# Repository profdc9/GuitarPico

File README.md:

# Guitar Pico

This is a guitar effects processor based on the Raspberry Pi Pico.  A video of some of the effects is at

https://www.youtube.com/watch?v=15d9mEu2koQ

It includes the following effects:

1.  Noise Gate
2.  Delay 
3.  Room (set up specific echoes at particular delays)
4.  Combine (mix together the signals from several effects)
5.  2nd order Bandpass filter
6.  2nd order Lowpass filter
7.  2nd order Highpass filter
8.  2nd order Allpass filter
9.  Tremolo (amplitude modulated by a low frequency oscillator)
10.  Vibrato (pitch modulated by a low frequency oscillator)
11.  Wah (bandpass filter with center frequency controlled by an external control like a pedal)
12.  AutoWah (bandpass filter with center frequency modulated by a low frequency oscillator)
13.  Envelope (bandpass filter with center frequency modulated by signal amplitude)
14.  Distortion (amplification resulting in saturation of the signal)
15.  Overdrive (selectable threshold for low signal / high signal amplitude gain)
16.  Compressor (amplifies weak signals to equal out overall amplitude of signal)
17.  Ring (ring modulator using low frequency oscillator)
18.  Flanger (pitch modulated by a low frequency oscillator, with feedback and combined with unmodulated signal)
19.  Chorus (pitch modulated by a low frequency oscillator, no feedback and combined with unmodulated signal)
20.  Phaser (signal run through multiple stages of all pass filters, combined with unmodulated signal)
21.  Backwards (plays the last samples backwards for weird swooping effect)
22.  PitchShift (allows shifting the pitch by variable amounts, useful for harmony-like effect)
23.  Whammy (pitch shift based on external control like a pedal)
24.  Octave (rectification and amplification of the signal with extreme distortion)
25.  Sinusoidal Oscillator (built in test signal source)

The effects may be cascaded, to up to 16 in a sequence.  The settings of a particular sequence of effects may be saved in flash memory.  Because the effects are processed one sample at a time in real-time, the lag due to the processing is only 50 microseconds.

There is a stomp pedal which may be used to one of four saved settings, based on which of the four buttons is stomped on.  It does not require power to operate.

The pedal has four potentiometers that may be assigned to control various aspects of effects operation.  There are also two external inputs.  These can be used with the stomp pedal, or with an expression pedal to control aspects of the effects.

There is also a feature to determine the frequency and note being played, to help with tuning a guitar.  Also, if plugged into USB, notes played on the guitar are sent as MIDI events to the PC to turn the guitar into a MIDI instruments.  However, this feature is imperfect (but this useful for tuning).

As well as a MIDI device, the guitar pedal appears as a COM port.  The effect settings may be retrieved from the pedal or programmed into the pedal through this interface using text commands at a prompt.  Type "HELP" for a list of the commands.  For example, typing "CONF 0 0" lists all of the current effects configuration data.  The data is output in the form of the commands used to reprogram the same state back into the device, so these may be directly copied into a text file and pasted back into a terminal to recreate the configuration.

There is also a VGA port that will be used to implement video effects.

The hardware is licensed under CC-BY-SA 4.0 and software under the zlib license (no warranty, yes commercial and noncommercial use), both open source licenses.

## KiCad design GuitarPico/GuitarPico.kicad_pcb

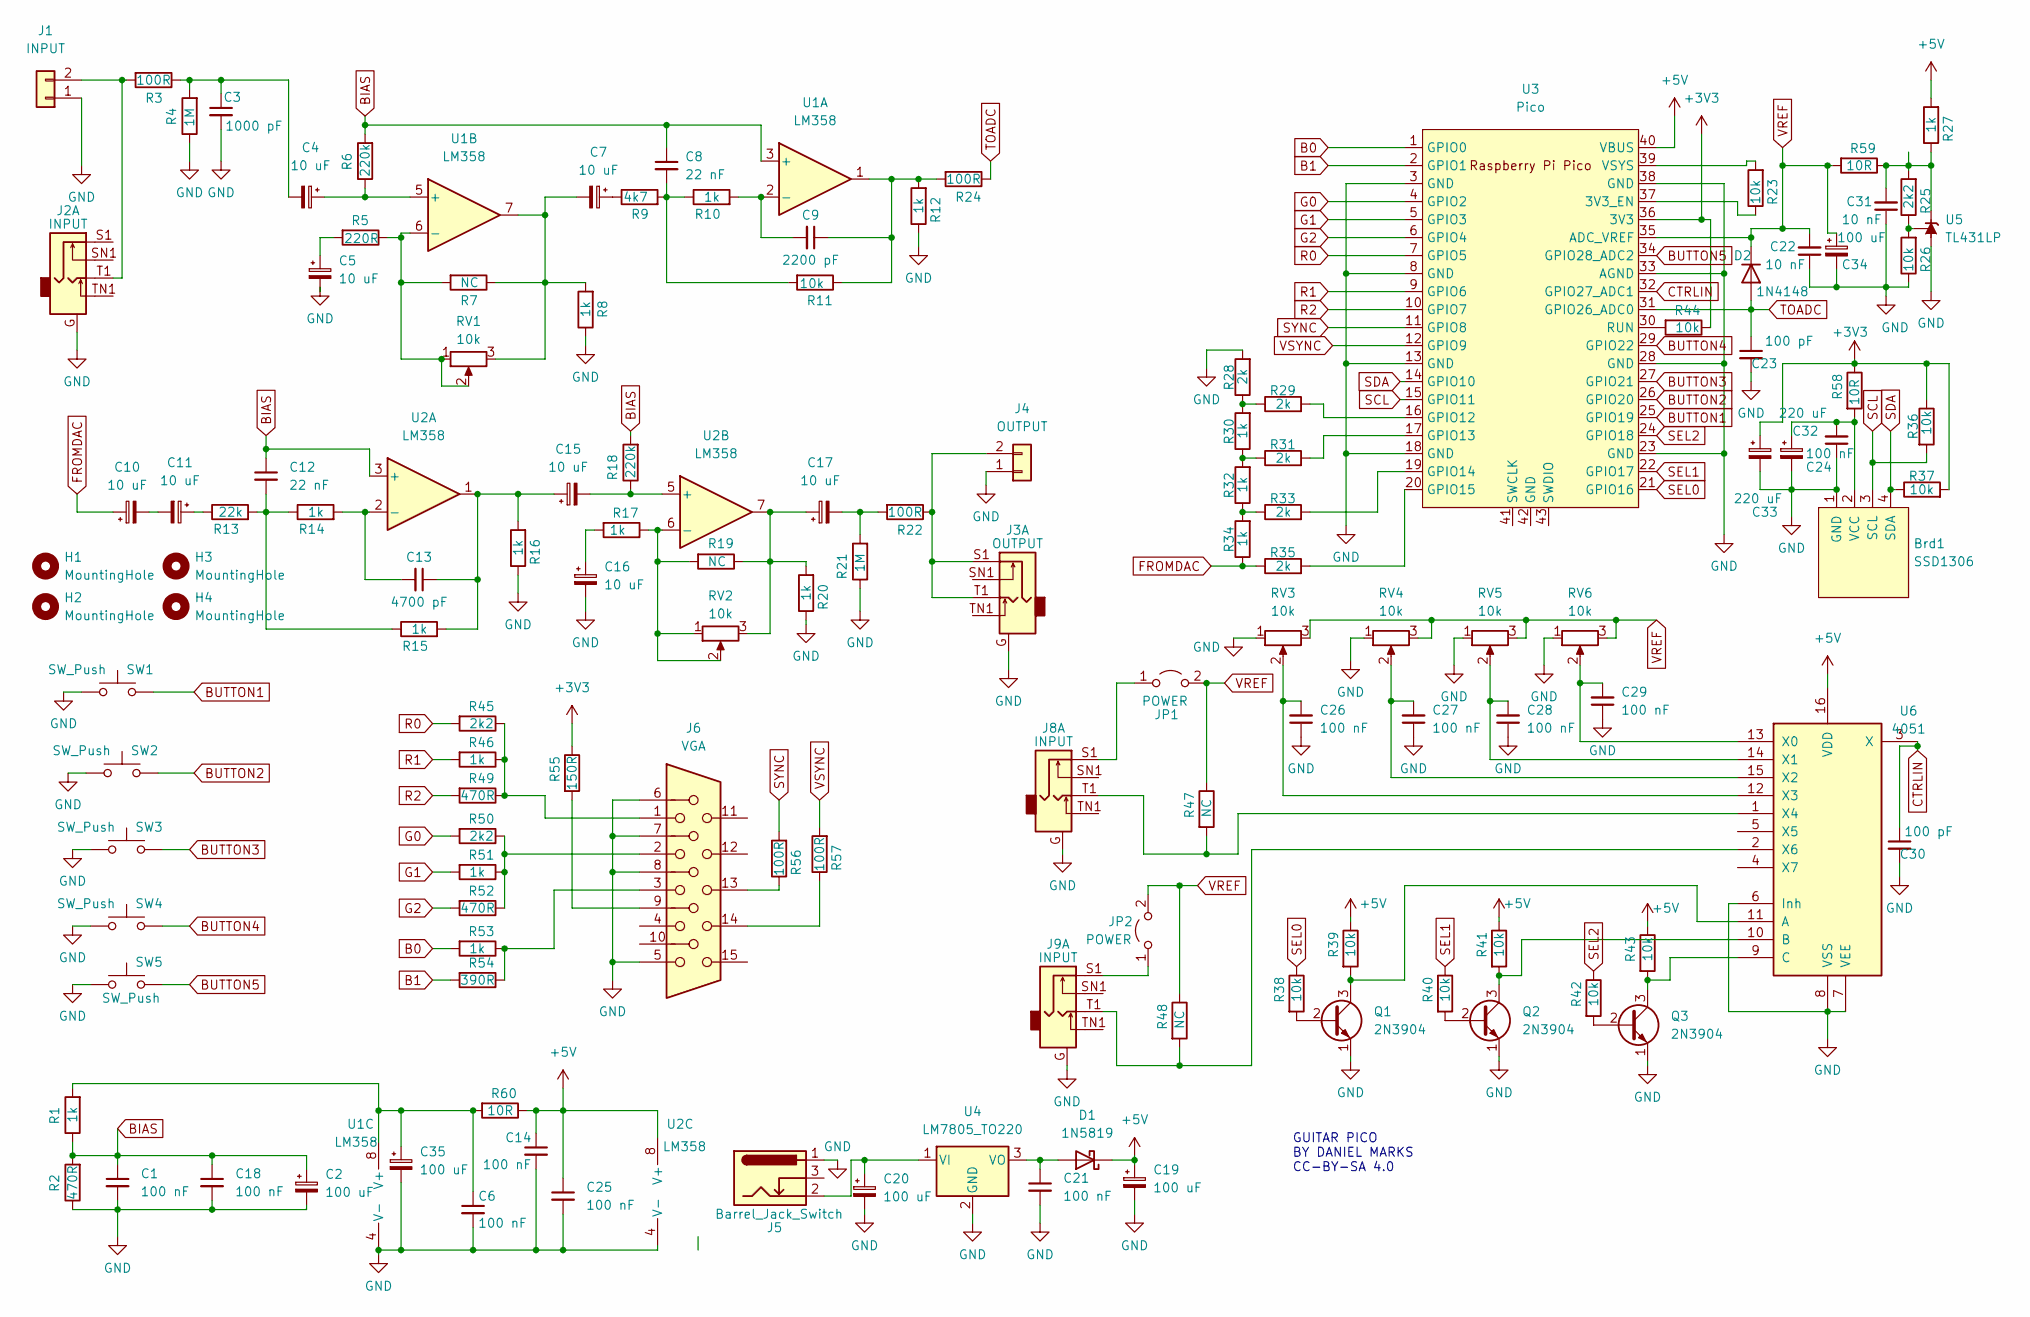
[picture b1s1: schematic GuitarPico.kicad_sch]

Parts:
Brd1: SSD1306; 128x64OLED
C1, C6, C14, C18, C21, C24, C25, C26, C27, C28, C29: 100 nF; C_Disc_D5.0mm_W2.5mm_P5.00mm
C2, C19, C20, C34, C35: 100 uF; CP_Radial_D5.0mm_P2.50mm
C3: 1000 pF; C_Disc_D5.0mm_W2.5mm_P5.00mm
C4, C5, C7, C10, C11, C15, C16, C17: 10 uF; CP_Radial_D5.0mm_P2.50mm
C8, C12: 22 nF; C_Disc_D5.0mm_W2.5mm_P5.00mm
C9: 2200 pF; C_Disc_D5.0mm_W2.5mm_P5.00mm
C13: 4700 pF; C_Disc_D5.0mm_W2.5mm_P5.00mm
C22, C31: 10 nF; C_Disc_D5.0mm_W2.5mm_P5.00mm
C23, C30: 100 pF; C_Disc_D5.0mm_W2.5mm_P5.00mm
C32, C33: 220 uF; CP_Radial_D5.0mm_P2.50mm
D1: 1N5819; D_DO-41_SOD81_P7.62mm_Horizontal
D2: 1N4148; D_DO-35_SOD27_P7.62mm_Horizontal
H1, H2, H3, H4: MountingHole; MountingHole_3.2mm_M3
J1: INPUT; TerminalBlock_bornier-2_P5.08mm
J2, J8, J9: INPUT; PJ-3240-35mm-stereo
J3: OUTPUT; PJ-3240-35mm-stereo
J4: OUTPUT; TerminalBlock_bornier-2_P5.08mm
J5: Barrel_Jack_Switch; BarrelJack_Horizontal
J6: VGA; DSUB-15-HD_Female_Horizontal_P2.29x1.98mm_EdgePinOffset3.03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
JP1, JP2: POWER; PinHeader_1x02_P2.54mm_Vertical
Q1, Q2, Q3: 2N3904; TO-92_Inline_Wide
R1, R8, R10, R12, R14, R15, R16, R17, R20, R27, R30, R32, R34, R46, R51, R53: 1k; R_Axial_DIN0207_L6.3mm_D2.5mm_P7.62mm_Horizontal
R2, R49, R52: 470R; R_Axial_DIN0207_L6.3mm_D2.5mm_P7.62mm_Horizontal
R3, R22, R24, R56, R57: 100R; R_Axial_DIN0207_L6.3mm_D2.5mm_P7.62mm_Horizontal
R4, R21: 1M; R_Axial_DIN0207_L6.3mm_D2.5mm_P7.62mm_Horizontal
R5: 220R; R_Axial_DIN0207_L6.3mm_D2.5mm_P7.62mm_Horizontal
R6, R18: 220k; R_Axial_DIN0207_L6.3mm_D2.5mm_P7.62mm_Horizontal
R7, R19, R47, R48: NC; R_Axial_DIN0207_L6.3mm_D2.5mm_P7.62mm_Horizontal
R9: 4k7; R_Axial_DIN0207_L6.3mm_D2.5mm_P7.62mm_Horizontal
R11, R23, R26, R36, R37, R38, R39, R40, R41, R42, R43, R44: 10k; R_Axial_DIN0207_L6.3mm_D2.5mm_P7.62mm_Horizontal
R13: 22k; R_Axial_DIN0207_L6.3mm_D2.5mm_P7.62mm_Horizontal
R25, R45, R50: 2k2; R_Axial_DIN0207_L6.3mm_D2.5mm_P7.62mm_Horizontal
R28, R29, R31, R33, R35: 2k; R_Axial_DIN0207_L6.3mm_D2.5mm_P7.62mm_Horizontal
R54: 390R; R_Axial_DIN0207_L6.3mm_D2.5mm_P7.62mm_Horizontal
R55: 150R; R_Axial_DIN0207_L6.3mm_D2.5mm_P7.62mm_Horizontal
R58, R59, R60: 10R; R_Axial_DIN0207_L6.3mm_D2.5mm_P7.62mm_Horizontal
RV1, RV2: 10k; Potentiometer_Big_Small_Combined
RV3, RV4, RV5, RV6: 10k; Potentiometer_Alps_RK09K_Single_Vertical
SW1, SW2, SW3, SW4, SW5: SW_Push; SW_PUSH_6mm
U1, U2: LM358; DIP-8_W7.62mm_Socket
U3: Pico; RPi_Pico_SMD_TH
U4: LM7805_TO220; TO-220-3_Vertical
U5: TL431LP; TO-92_Inline_Wide
U6: 4051; DIP-16_W7.62mm_Socket

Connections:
+3V3: C33.1, R36.1, R37.2, R44.1, R55.1, R58.1, U3.36 (3V3)
+5V: C14.1, C19.1, C25.1, D1.1 (K), R27.2, R39.1, R41.1, R43.1, R60.1, U2.8 (V+), U3.40 (VBUS), U6.16 (VDD)
B0: R53.2, U3.1 (GPIO0)
B1: R54.2, U3.2 (GPIO1)
BIAS: C1.1, C2.1, C8.1, C12.1, C18.1, R1.1, R2.2, R6.2, R18.2, U1.3 (+), U2.3 (+)
BUTTON1: SW1.2, U3.25 (GPIO19)
BUTTON2: SW2.2, U3.26 (GPIO20)
BUTTON3: SW3.2, U3.27 (GPIO21)
BUTTON4: SW4.2, U3.29 (GPIO22)
BUTTON5: SW5.2, U3.34 (GPIO28_ADC2)
CTRLIN: C30.1, U3.32 (GPIO27_ADC1), U6.3 (X)
FROMDAC: C10.1, R34.1, R35.1
G0: R50.2, U3.4 (GPIO2)
G1: R51.2, U3.5 (GPIO3)
G2: R52.2, U3.6 (GPIO4)
GND: Brd1.1 (GND), C1.2, C2.2, C3.2, C5.2, C6.2, C14.2, C16.2, C18.2, C19.2, C20.2, C21.2, C22.1, C23.2, C24.1, C25.2, C26.1, C27.1, C28.1, C29.1, C30.2, C31.1, C32.2, C33.2, C34.2, C35.2, J1.1, J2.G, J3.G, J4.1, J5.1, J6.5, J6.6, J6.7, J6.8, J8.G, J9.G, Q1.1 (E), Q2.1 (E), Q3.1 (E), R2.1, R4.1, R8.1, R12.1, R16.1, R20.1, R21.1, R26.1, R28.2, RV3.1, RV4.1, RV5.1, RV6.1, SW1.1, SW2.1, SW3.1, SW4.1, SW5.1, U1.4 (V-), U2.4 (V-), U3.3 (GND), U3.8 (GND), U3.13 (GND), U3.18 (GND), U3.23 (GND), U3.28 (GND), U3.33 (AGND), U3.38 (GND), U4.2 (GND), U5.2 (A), U6.6 (Inh), U6.7 (VEE), U6.8 (VSS)
unnamed: Brd1.2 (VCC), C24.2, C32.1, R58.2
unnamed: C3.1, C4.2, R3.1, R4.2
unnamed: C5.1, R5.2
unnamed: C7.1, R9.1
unnamed: C7.2, R7.1, R8.2, RV1.3, U1.7
unnamed: C8.2, R9.2, R10.1, R11.2
unnamed: C9.1, R11.1, R12.2, R24.2, U1.1
unnamed: C10.2, C11.2
unnamed: C11.1, R13.1
unnamed: C12.2, R13.2, R14.1, R15.1
unnamed: C13.1, C15.1, R15.2, R16.2, U2.1
unnamed: C16.1, R17.2
unnamed: C17.1, R19.1, R20.2, RV2.3, U2.7
unnamed: C17.2, R21.2, R22.2
unnamed: C21.1, D1.2 (A), U4.3 (VO)
unnamed: J1.2, J2.T1, R3.2
unnamed: J3.S1, J3.T1, J4.2, R22.1
unnamed: J6.1, R45.1, R46.1, R49.1
unnamed: J6.2, R50.1, R51.1, R52.1
unnamed: J6.3, R53.1, R54.1
unnamed: J6.9, R55.2
unnamed: J6.13, R56.1
unnamed: J6.14, R57.1
unnamed: J8.S1, JP1.1 (A)
unnamed: J9.S1, JP2.1 (A)
unnamed: Q1.2 (B), R38.2
unnamed: Q1.3 (C), R39.2, U6.11 (A)
unnamed: Q2.2 (B), R40.2
unnamed: Q2.3 (C), R41.2, U6.10 (B)
unnamed: Q3.2 (B), R42.2
unnamed: Q3.3 (C), R43.2, U6.9 (C)
unnamed: R28.1, R29.1, R30.2
unnamed: R30.1, R31.1, R32.2
unnamed: R32.1, R33.1, R34.2
unnamed: C9.2, R10.2, U1.2 (-)
unnamed: C4.1, R6.1, U1.5 (+)
unnamed: R5.1, R7.2, RV1.1, RV1.2, U1.6 (-)
unnamed: C6.1, C35.1, R1.2, R60.2, U1.8 (V+)
unnamed: C13.2, R14.2, U2.2 (-)
unnamed: C15.2, R18.1, U2.5 (+)
unnamed: R17.1, R19.2, RV2.1, RV2.2, U2.6 (-)
unnamed: R23.1, U3.37 (3V3_EN)
unnamed: R29.2, U3.16 (GPIO12)
unnamed: R31.2, U3.17 (GPIO13)
unnamed: R33.2, U3.19 (GPIO14)
unnamed: R35.2, U3.20 (GPIO15)
unnamed: R44.2, U3.30 (RUN)
unnamed: R23.2, U3.39 (VSYS)
unnamed: C20.1, J5.2, U4.1 (VI)
unnamed: C31.2, R25.2, R27.1, R59.1, U5.3 (K)
unnamed: R25.1, R26.2, U5.1 (REF)
unnamed: C29.2, RV6.2, U6.13 (X0)
unnamed: C28.2, RV5.2, U6.14 (X1)
unnamed: C27.2, RV4.2, U6.15 (X2)
unnamed: C26.2, RV3.2, U6.12 (X3)
unnamed: J8.T1, R47.2, U6.1 (X4)
unnamed: J9.T1, R48.2, U6.2 (X6)
R0: R45.2, U3.7 (GPIO5)
R1: R46.2, U3.9 (GPIO6)
R2: R49.2, U3.10 (GPIO7)
SCL: Brd1.3 (SCL), R36.2, U3.15 (GPIO11)
SDA: Brd1.4 (SDA), R37.1, U3.14 (GPIO10)
SEL0: R38.1, U3.21 (GPIO16)
SEL1: R40.1, U3.22 (GPIO17)
SEL2: R42.1, U3.24 (GPIO18)
SYNC: R56.2, U3.11 (GPIO8)
TOADC: C23.1, D2.2 (A), R24.1, U3.31 (GPIO26_ADC0)
VREF: C22.2, C34.1, D2.1 (K), JP1.2 (B), JP2.2 (B), R47.1, R48.1, R59.2, RV3.3, RV4.3, RV5.3, RV6.3, U3.35 (ADC_VREF)
VSYNC: R57.2, U3.12 (GPIO9)

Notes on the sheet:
GUITAR PICO BY DANIEL MARKS CC-BY-SA 4.0

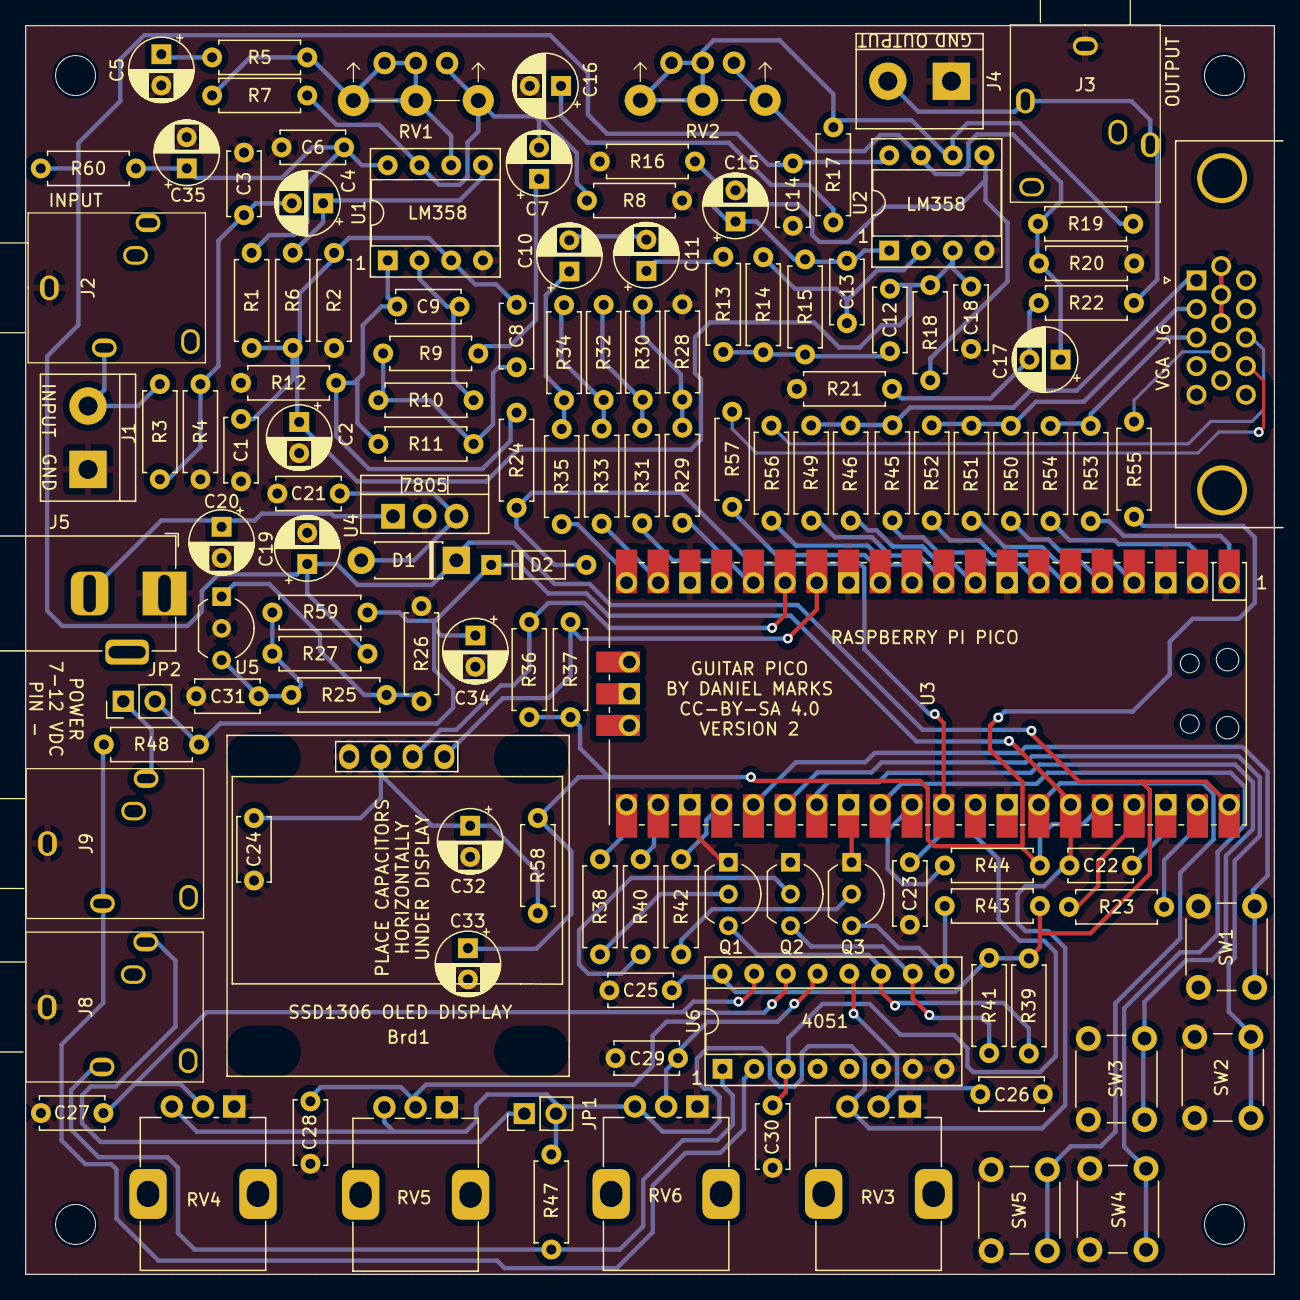
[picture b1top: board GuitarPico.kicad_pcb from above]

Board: 2 copper layers, 100.0 x 100.0 mm, 132 parts (0 on the bottom side), 85 nets.

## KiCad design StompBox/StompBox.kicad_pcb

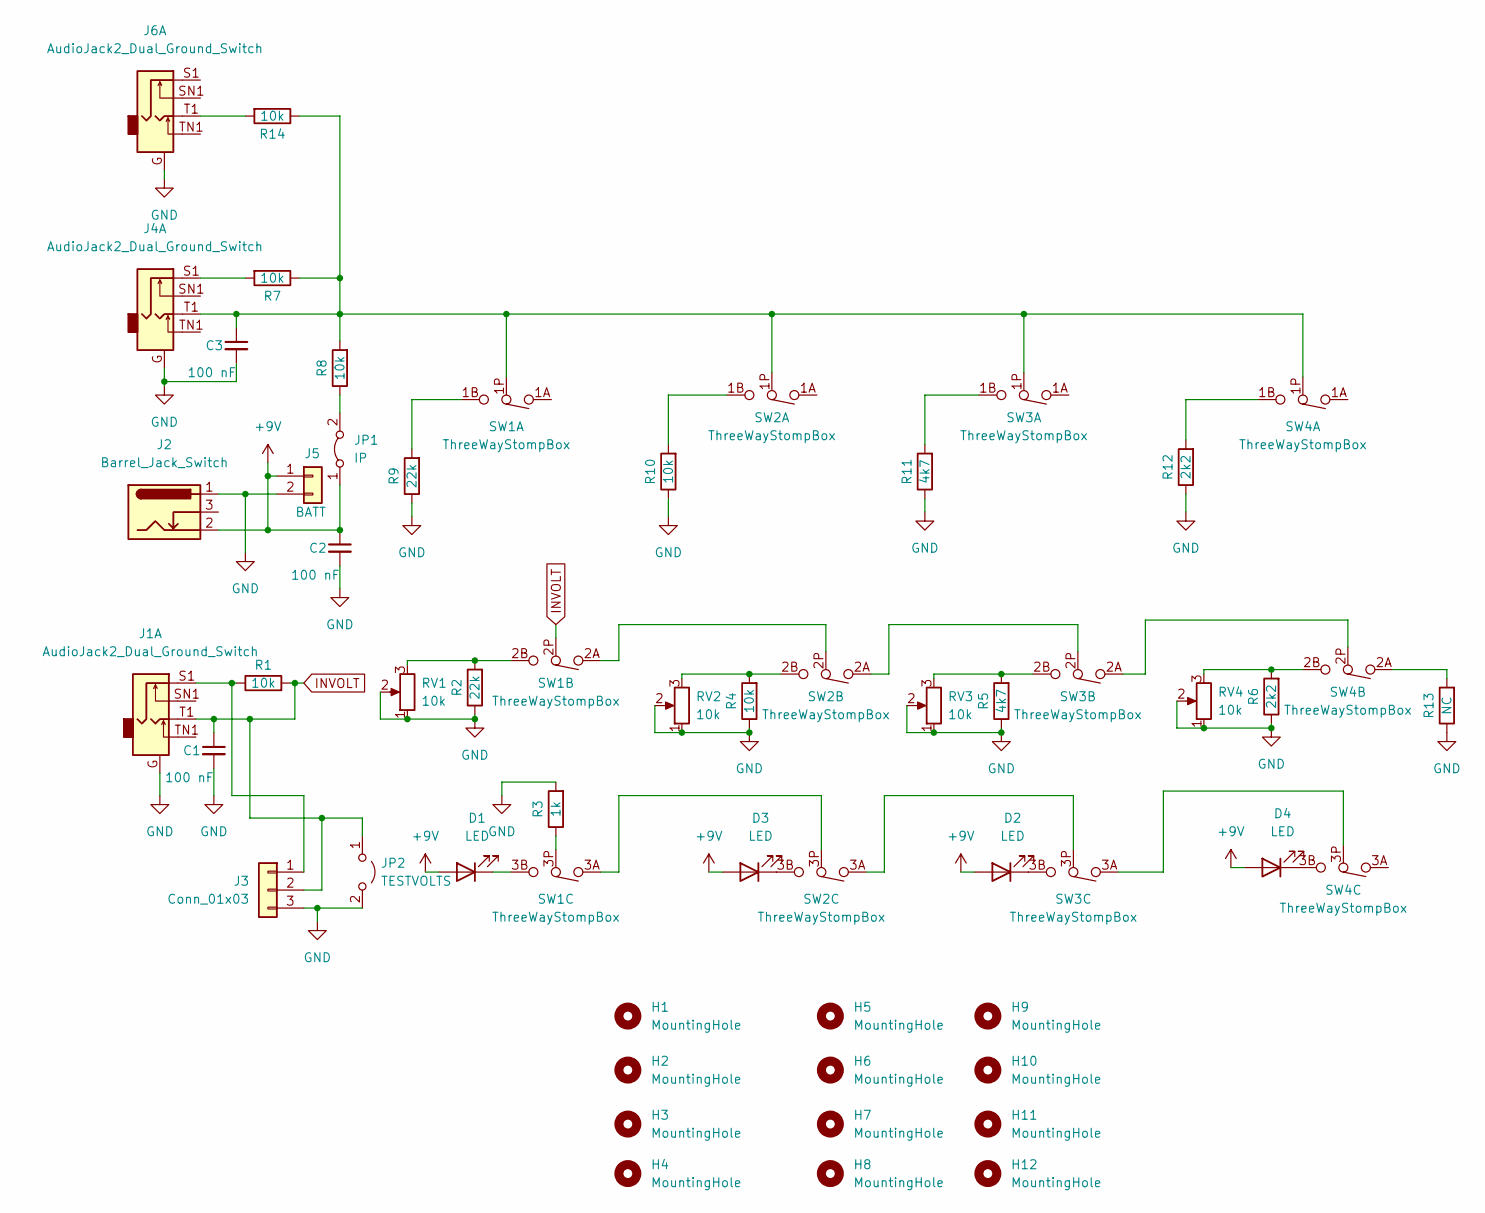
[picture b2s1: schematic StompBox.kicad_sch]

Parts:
C1, C2, C3: 100 nF; C_Disc_D5.0mm_W2.5mm_P5.00mm
D1, D2, D3, D4: LED; LED_D5.0mm
H1, H2, H3, H4, H5, H6, H7, H8, H9, H10, H11, H12: MountingHole; MountingHole_3.2mm_M3
J1, J4, J6: AudioJack2_Dual_Ground_Switch; PJ-3240-35mm-stereo
J2: Barrel_Jack_Switch; BarrelJack_Horizontal
J3: Conn_01x03; TerminalBlock_bornier-3_P5.08mm
J5: BATT; PinHeader_1x02_P2.54mm_Vertical
JP1: IP; PinHeader_1x02_P2.54mm_Vertical
JP2: TESTVOLTS; PinHeader_1x02_P2.54mm_Vertical
R1, R4, R7, R8, R10, R14: 10k; R_Axial_DIN0207_L6.3mm_D2.5mm_P7.62mm_Horizontal
R2, R9: 22k; R_Axial_DIN0207_L6.3mm_D2.5mm_P7.62mm_Horizontal
R3: 1k; R_Axial_DIN0207_L6.3mm_D2.5mm_P7.62mm_Horizontal
R5, R11: 4k7; R_Axial_DIN0207_L6.3mm_D2.5mm_P7.62mm_Horizontal
R6, R12: 2k2; R_Axial_DIN0207_L6.3mm_D2.5mm_P7.62mm_Horizontal
R13: NC; R_Axial_DIN0207_L6.3mm_D2.5mm_P7.62mm_Horizontal
RV1, RV2, RV3, RV4: 10k; Potentiometer_Bourns_3296W_Vertical
SW1, SW2, SW3, SW4: ThreeWayStompBox; ThreeWayStompBoxSwitch

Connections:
+9V: C2.1, D1.2 (A), D2.2 (A), D3.2 (A), D4.2 (A), J2.2, J5.1, JP1.1 (A)
GND: C1.2, C2.2, C3.2, J1.G, J2.1, J3.3, J4.G, J5.2, J6.G, JP2.2 (B), R2.1, R3.2, R4.1, R5.1, R6.1, R9.1, R10.1, R11.1, R12.1, R13.1, RV1.1, RV1.2, RV2.1, RV2.2, RV3.1, RV3.2, RV4.1, RV4.2
INVOLT: C1.1, J1.T1, J3.2, JP2.1 (A), R1.2, SW1.2P
unnamed: C3.1, J4.T1, R7.1, R8.2, R14.1, SW1.1P, SW2.1P, SW3.1P, SW4.1P
unnamed: D1.1 (K), SW1.3B
unnamed: D2.1 (K), SW3.3B
unnamed: D3.1 (K), SW2.3B
unnamed: D4.1 (K), SW4.3B
unnamed: J1.S1, J3.1, R1.1
unnamed: J4.S1, R7.2
unnamed: J6.T1, R14.2
unnamed: JP1.2 (B), R8.1
unnamed: R2.2, RV1.3, SW1.2B
unnamed: R3.1, SW1.3P
unnamed: R4.2, RV2.3, SW2.2B
unnamed: R5.2, RV3.3, SW3.2B
unnamed: R6.2, RV4.3, SW4.2B
unnamed: R9.2, SW1.1B
unnamed: R10.2, SW2.1B
unnamed: R11.2, SW3.1B
unnamed: R12.2, SW4.1B
unnamed: R13.2, SW4.2A
unnamed: SW1.2A, SW2.2P
unnamed: SW1.3A, SW2.3P
unnamed: SW2.2A, SW3.2P
unnamed: SW2.3A, SW3.3P
unnamed: SW3.2A, SW4.2P
unnamed: SW3.3A, SW4.3P

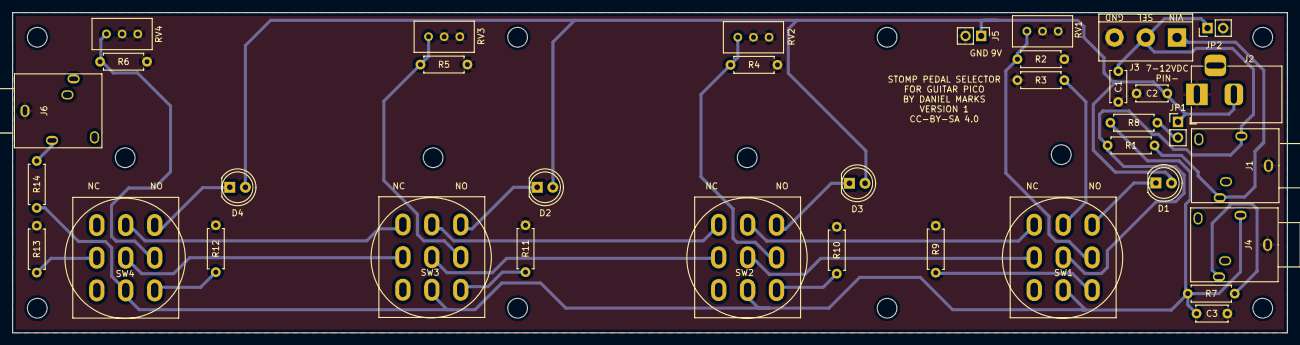
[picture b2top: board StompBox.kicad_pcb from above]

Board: 2 copper layers, 207.0 x 52.0 mm, 49 parts (0 on the bottom side), 28 nets.

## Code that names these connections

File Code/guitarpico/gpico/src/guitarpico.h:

/* guitarpico.h

*/

/*
   Copyright (c) 2024 Daniel Marks

  This software is provided 'as-is', without any express or implied
  warranty. In no event will the authors be held liable for any damages
  arising from the use of this software.

  Permission is granted to anyone to use this software for any purpose,
  including commercial applications, and to alter it and redistribute it
  freely, subject to the following restrictions:

  1. The origin of this software must not be misrepresented; you must not
   claim that you wrote the original software. If you use this software
   in a product, an acknowledgment in the product documentation would be
   appreciated but is not required.
  2. Altered source versions must be plainly marked as such, and must not be
   misrepresented as being the original software.
  3. This notice may not be removed or altered from any source distribution.
*/

#ifndef _GUITARPICO_H
#define _GUITARPICO_H

#include "pico.h"
#include "pico/stdlib.h"
#include "pico/multicore.h"
#include "hardware/clocks.h"
#include "hardware/pio.h"
#include "hardware/pwm.h"
#include "hardware/adc.h"
#include "hardware/dma.h"
#include "hardware/timer.h"
#include "hardware/sync.h"
#include "hardware/flash.h"

#define DMB() __dmb()

#define DAC_PWM_B3 15
#define DAC_PWM_B2 14
#define DAC_PWM_B1 13
#define DAC_PWM_B0 12

#define DAC_PWM_WRAP_VALUE 0x400

#define ADC_AUDIO_IN 26
#define ADC_CONTROL_IN 27
#define ADC_MAX_VALUE 4096
#define ADC_PREC_VALUE 16384

#define GPIO_ADC_SEL0 16
#define GPIO_ADC_SEL1 17
#define GPIO_ADC_SEL2 18

#define GPIO_BUTTON1 19
#define GPIO_BUTTON2 20
#define GPIO_BUTTON3 21
#define GPIO_BUTTON4 22
#define GPIO_BUTTON5 28

#define GUITARPICO_SAMPLERATE 25000u
#define POT_MAX_VALUE 16384u

#ifndef LED_PIN
#define LED_PIN 25
#endif /* LED_PIN */

#ifdef __cplusplus
extern "C"
{
#endif

uint16_t read_potentiometer_value(uint v);

#define POTENTIOMETER_VALUE_SENSITIVITY 20
#define POTENTIOMETER_MAX 6

#ifdef __cplusplus
}
#endif


#endif /* _GUITARPICO_H */

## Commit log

2023-09-02 Before replacing with buttons
2023-09-02 replaced with buttons
2023-09-02 Fixed TL431 wiring problem
2023-09-02 Added VGA connector!
2023-09-03 Flipped resistor
2023-09-15 Added CAD pedal
2023-09-17 Adjusted dimensions
2023-09-17 Added simulations
2023-12-11 Added FIR Filter examples
2023-12-25 First example of guitarpico project
2023-12-27 Working pass thru
2023-12-28 Added ui elements
2023-12-30 can now edit parameters
2023-12-31 Working IIR filters
2024-01-01 Added some more effects
2024-01-03 Added room guitar effect
2024-01-04 Added source unit
2024-01-05 Modified source unit code
2024-01-06 Awesome sounding envelope pedal
2024-01-07 Before adding flash save
2024-01-07 Added flash save support
2024-01-08 Added a command line!
2024-01-09 Added some more command line support
2024-01-13 Try phaser again
2024-01-14 Finally got a great sounding Phaser!
2024-01-14 Added chorus
2024-01-16 Added primitive pitch shift
2024-01-16 Much improved pitch shift
2024-01-20 Pitch change
2024-01-22 First version of pitch measure
2024-01-23 Working pitch and note mode
2024-01-24 I think I fixed problem with sound blanking out
2024-01-27 Added compressor
2024-01-27 Changed to non stdio USB
2024-02-01 Decently working pitch to usb midi
2024-02-11 Added a stompbox
2024-02-24 Stompbox JLCPCB
2024-03-02 Minor code fixes
2024-03-09 Added whammy bar!
2024-03-09 Added new README
2024-03-20 Added support for stomp box
2024-04-28 Refactored dsp structures into two parts
2024-07-27 Backported fixed to DSP library from synthesizer
2025-01-04 Moved to new computer
2026-01-17 Added STL file for pedal enclosure
